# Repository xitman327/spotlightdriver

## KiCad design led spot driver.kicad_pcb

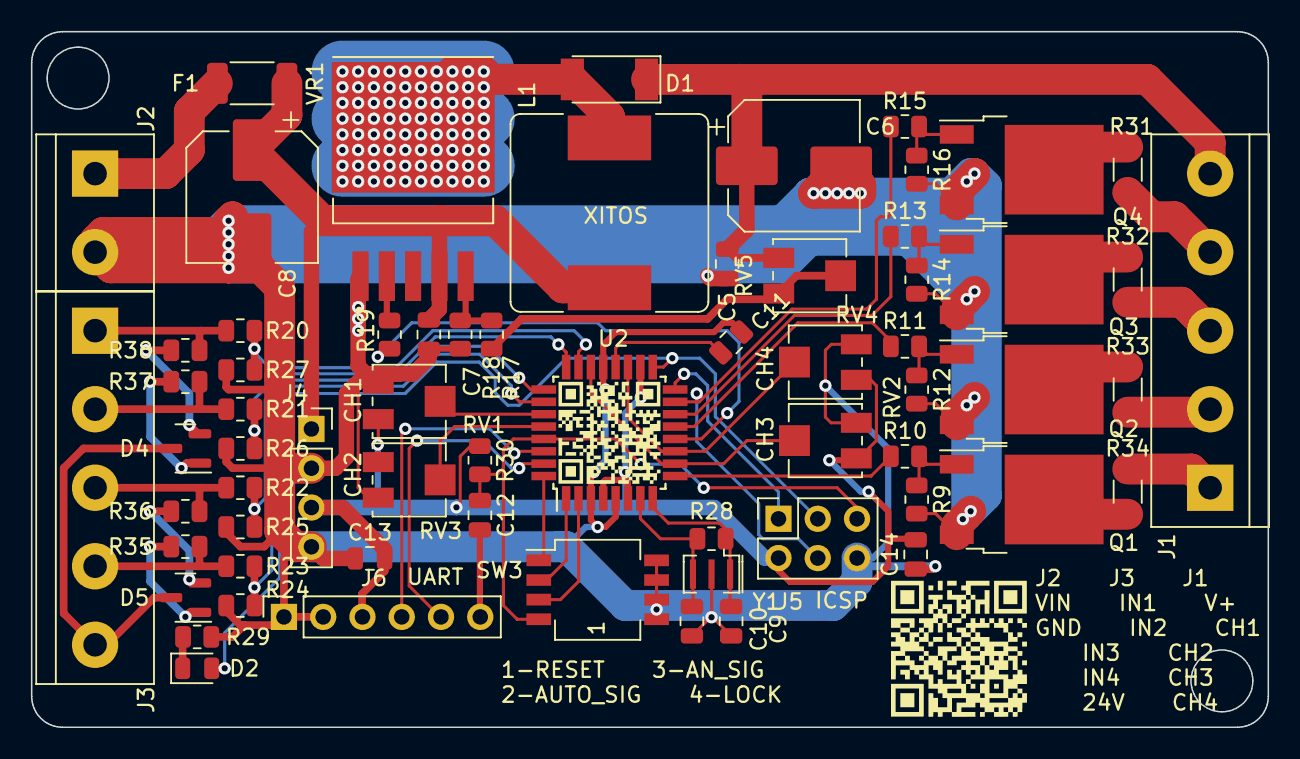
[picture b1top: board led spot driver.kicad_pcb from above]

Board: 2 copper layers, 80.0 x 45.0 mm, 65 parts (0 on the bottom side), 56 nets.

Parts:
C5, C7, C9, C10, C11, C12, C13, C14: C_Small; C_0805_2012Metric
C6, C8: C_Polarized_Small; CP_Elec_8x5.4
D1: D_Schottky_Small; D_MELF
D2: LED_Small; LED_0805_2012Metric
D4, D5: MMBZxx; SOT-23
F1: Fuse_Small; Fuse_2010_5025Metric
J1, J3: Conn_01x05; TerminalBlock_bornier-5_P5.08mm
J2: Conn_01x02; TerminalBlock_bornier-2_P5.08mm
J4: Conn_01x04; PinSocket_1x04_P2.54mm_Vertical
J5: Conn_02x03_Odd_Even; PinSocket_2x03_P2.54mm_Vertical
J6: Conn_01x06; PinSocket_1x06_P2.54mm_Vertical
L1: L_Small; L_Bourns_SRR1260
Q1, Q2, Q3, Q4: Q_NMOS_GDS; TO-252-2
R9, R10, R11, R12, R13, R14, R15, R16, R17, R18, R19, R20, R21, R22, R23, R24, R25, R26, R27, R28, R29, R30, R35, R36, R37, R38: R_Small; R_0805_2012Metric
R31, R32, R33, R34: R_Small; R_1206_3216Metric
RV1, RV2, RV3, RV4, RV5: R_Potentiometer_Small; Potentiometer_Bourns_3314J_Vertical
SW3: SW_DIP_x04; SW_DIP_SPSTx04_Slide_Copal_CHS-04B_W7.62mm_P1.27mm
U2: ATmega328P-A; TQFP-32_7x7mm_P0.8mm
VR1: XL6009; DPAK170P1435X465-6N
Y1: Crystal_GND2; Resonator_SMD_Murata_CSTxExxV-3Pin_3.0x1.1mm

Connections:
+5V: C13.2, C14.2, J4.3, J5.2, J6.3, R30.1, RV1.3, RV2.1, RV3.1, RV4.1, U2.4 (VCC), U2.6 (VCC), U2.18 (AVCC)
/A1: R20.2, R27.2, U2.23 (PC0)
/A2: R21.2, R26.2, U2.24 (PC1)
/A3: R22.2, R25.2, U2.25 (PC2)
/A4: R23.2, R24.2, U2.26 (PC3)
/PWM1: J5.4, R15.1, U2.15 (PB3)
/PWM2: R13.1, U2.14 (PB2)
/PWM3: R11.1, U2.13 (PB1)
/PWM4: R10.1, U2.9 (PD5)
/T1: RV1.2, U2.27 (PC4)
/T2: RV3.2, U2.28 (PC5)
/T3: RV2.2, U2.10 (PD6), U2.22 (ADC7)
/T4: RV4.2, U2.11 (PD7), U2.19 (ADC6)
/_DCDC_SW: D1.2 (A), L1.2, VR1.3 (SW), VR1.6 (SW)
/_dtr: C12.2, J6.6
/_miso: J5.1, U2.16 (PB4)
/_rst: C12.1, J5.5, R30.2, SW3.4, U2.29 (~RESET/PC6)
/_rx: J6.4, U2.30 (PD0)
/_sck: D2.2 (A), J5.3, U2.17 (PB5)
/_tx: J6.5, U2.31 (PD1)
/bk_EN: R19.2, U2.12 (PB0)
/usr0: SW3.3, U2.2 (PD4)
/usr1: SW3.2, U2.1 (PD3)
/usr2: SW3.1, U2.32 (PD2)
GND: C5.2, C6.2, C7.2, C8.2, C9.2, C10.2, C11.1, C13.1, C14.1, J2.2, J4.2, J4.4, J5.6, J6.1, J6.2, Q1.3 (S), Q2.3 (S), Q3.3 (S), Q4.3 (S), R9.2, R12.2, R14.2, R16.2, R18.1, R24.1, R25.1, R26.1, R27.1, R29.2, RV1.1, RV2.3, RV3.3, RV4.3, SW3.5, SW3.6, SW3.7, SW3.8, U2.3 (GND), U2.5 (GND), U2.21 (GND), VR1.1 (GND), Y1.2
unnamed: D2.1 (K), R29.1
unnamed: D4.3 (A), D5.3 (A), J3.5
unnamed: D4.1 (K), R37.1
unnamed: D4.2 (K), R38.1
unnamed: D5.2 (K), R36.1
unnamed: D5.1 (K), R35.1
unnamed: J1.1, R34.2
unnamed: J1.2, R33.2
unnamed: J1.3, R32.2
unnamed: J1.4, R31.2
unnamed: F1.1, J2.1
unnamed: J3.1, R20.1, R38.2
unnamed: J3.2, R21.1, R37.2
unnamed: J3.3, R22.1, R36.2
unnamed: J3.4, R23.1, R35.2
unnamed: Q1.2 (D), R34.1
unnamed: Q1.1 (G), R9.1, R10.2
unnamed: Q2.2 (D), R33.1
unnamed: Q2.1 (G), R11.2, R12.1
unnamed: Q3.2 (D), R32.1
unnamed: Q3.1 (G), R13.2, R14.1
unnamed: Q4.2 (D), R31.1
unnamed: Q4.1 (G), R15.2, R16.1
unnamed: R17.2, RV5.2, RV5.3
unnamed: C11.2, U2.20 (AREF)
unnamed: C10.1, R28.1, U2.7 (XTAL1/PB6), Y1.3
unnamed: C9.1, R28.2, U2.8 (XTAL2/PB7), Y1.1
unnamed: R19.1, VR1.2 (EN)
unnamed: R17.1, R18.2, VR1.5 (FB)
VBUS: C5.1, C6.1, D1.1 (K), J1.5, RV5.1
VCC: C7.1, C8.1, F1.2, J4.1, L1.1, VR1.4 (VIN)
